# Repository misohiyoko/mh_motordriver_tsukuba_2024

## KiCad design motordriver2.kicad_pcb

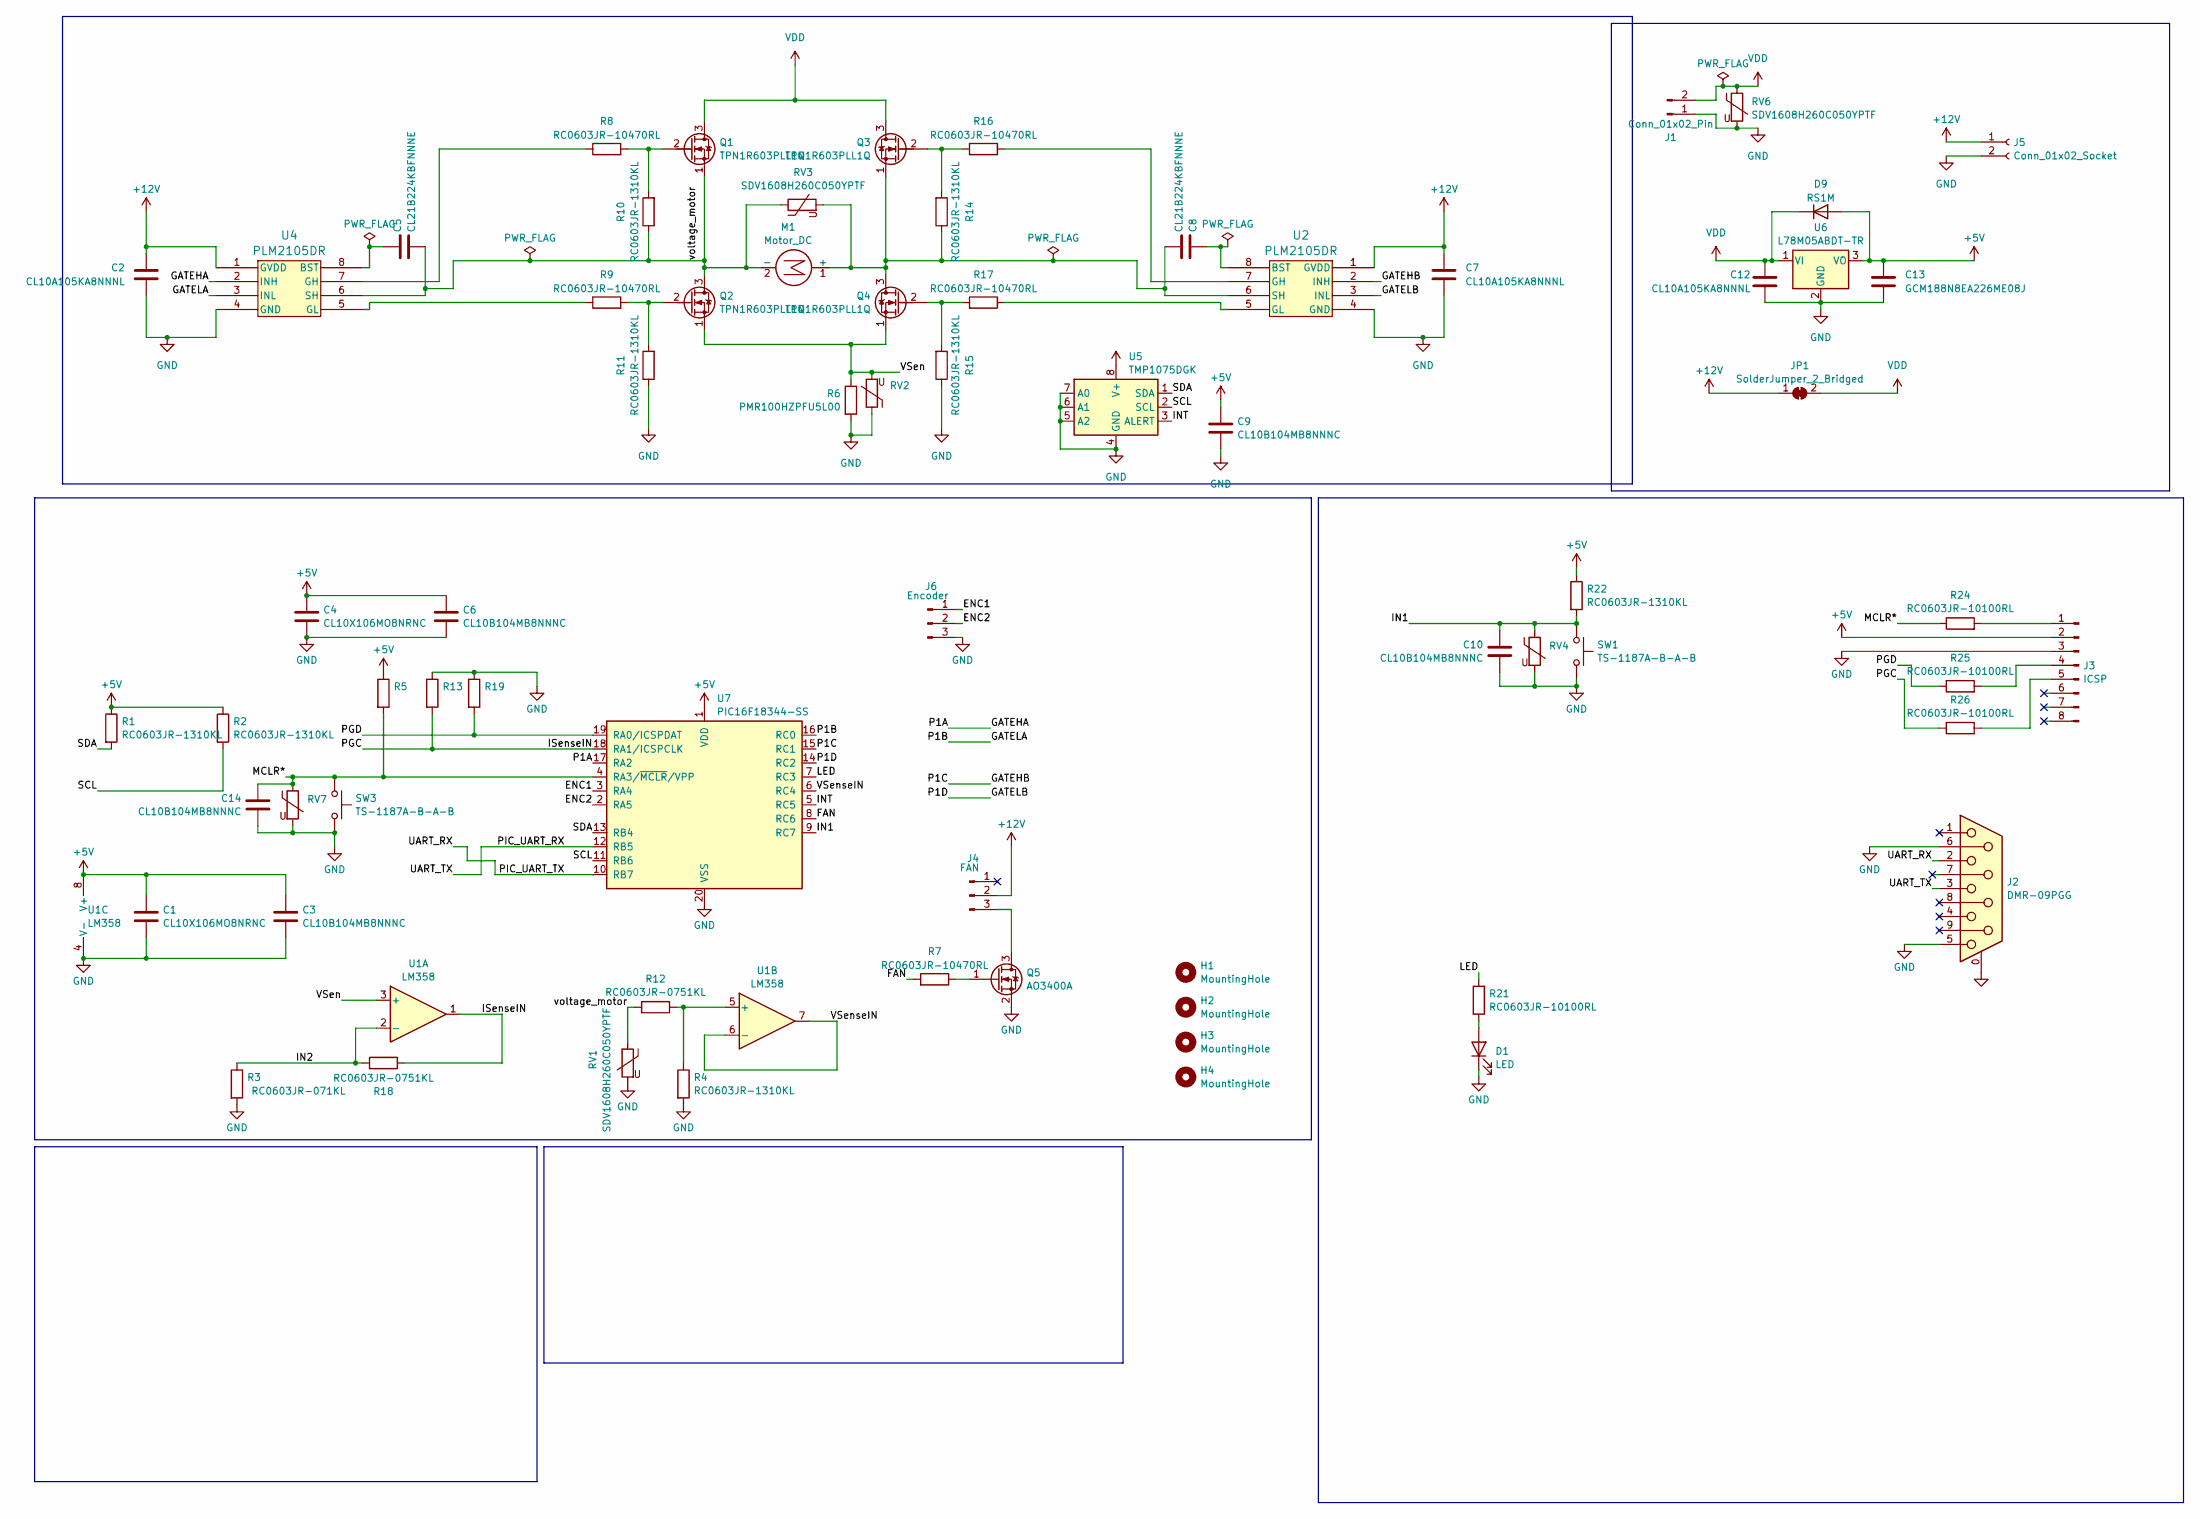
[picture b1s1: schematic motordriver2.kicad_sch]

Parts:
C1, C4: CL10X106MO8NRNC; C_0603_1608Metric; LCSC C19702
C2, C7: CL10A105KA8NNNL; C_0603_1608Metric; LCSC C15849
C3, C6, C9, C10, C14: CL10B104MB8NNNC; C_0603_1608Metric; LCSC C14663
C5, C8: CL21B224KBFNNNE; C_0805_2012Metric; LCSC C5378
C12: CL10A105KA8NNNL; C_0603_1608Metric_Pad1.08x0.95mm_HandSolder; LCSC C1848
C13: GCM188N8EA226ME08J; C_0603_1608Metric_Pad1.08x0.95mm_HandSolder; LCSC C45783
D1: LED; LED_0603_1608Metric_Pad1.05x0.95mm_HandSolder
D9: RS1M; D_SMA_Handsoldering; LCSC C8678
H1, H2, H3, H4: MountingHole; MountingHole_3.2mm_M3_Pad
J1: Conn_01x02_Pin; AMASS_XT60IPW-M_1x03_P7.20mm_Horizontal
J2: DMR-09PGG; DSUB-9_Female_Horizontal_P2.77x2.84mm_EdgePinOffset7.70mm_H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; LCSC C2846087
J3: ICSP; PinSocket_1x08_P2.54mm_Vertical
J4: FAN; PinSocket_1x03_P2.54mm_Vertical
J5: Conn_01x02_Socket; PinSocket_1x02_P2.54mm_Vertical
J6: Encoder; PinSocket_1x03_P2.54mm_Vertical
JP1: SolderJumper_2_Bridged; SolderJumper-2_P1.3mm_Bridged_RoundedPad1.0x1.5mm
M1: Motor_DC; AMASS_XT60PW-F_1x02_P7.20mm_Horizontal
Q1, Q2, Q3, Q4: TPN1R603PLL1Q; TSON Advance_TOS; LCSC C516183
Q5: AO3400A; SOT-23
R1, R2, R4, R5, R13, R19, R22: RC0603JR-1310KL; R_0603_1608Metric; LCSC C25744
R3: RC0603JR-071KL; R_0603_1608Metric
R6: PMR100HZPFU5L00; R_2512_6332Metric
R7, R8, R9, R16, R17: RC0603JR-10470RL; R_0603_1608Metric; LCSC C23182
R10, R11, R14, R15: RC0603JR-1310KL; R_0603_1608Metric; LCSC C25804
R12, R18: RC0603JR-0751KL; R_0603_1608Metric; LCSC C23196
R21, R24, R25, R26: RC0603JR-10100RL; R_0603_1608Metric; LCSC C17415
RV1, RV2, RV3, RV6: SDV1608H260C050YPTF; R_0603_1608Metric; LCSC C96738
RV4, RV7: AVR-M1005C080MTADB; R_0402_1005Metric; LCSC C92017
SW1, SW3: TS-1187A-B-A-B; SW_Push_1P1T_XKB_TS-1187A; LCSC C318884
U1: LM358; SOIC-8_3.9x4.9mm_P1.27mm; LCSC C7950
U2, U4: PLM2105DR; SOIC8_D_TEX
U5: TMP1075DGK; VSSOP-8_3.0x3.0mm_P0.65mm; LCSC C2864807
U6: L78M05ABDT-TR; TO-252-2; LCSC C58069
U7: PIC16F18344-SS; SSOP-20_5.3x7.2mm_P0.65mm

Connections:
+5V: C1.1, C3.1, C4.1, C6.1, C9.1, C13.1, D9.2 (A), J3.2, R1.1, R2.1, R5.1, R22.1, U1.8 (V+), U5.8 (V+), U6.3 (VO), U7.1 (VDD)
+12V: C2.1, C7.1, J4.2, J5.1, JP1.1 (A), U2.1 (GVDD), U4.1 (GVDD)
/ENC1: J6.1, U7.3 (RA4)
/ENC2: J6.2, U7.2 (RA5)
/FAN: R7.2, U7.8 (RC6)
/GATEHA: U4.2 (INH), U7.17 (RA2)
/GATEHB: U2.2 (INH), U7.15 (RC1)
/GATELA: U4.3 (INL), U7.16 (RC0)
/GATELB: U2.3 (INL), U7.14 (RC2)
/IN1: C10.1, R22.2, RV4.1, SW1.1, U7.9 (RC7)
/IN2: R3.1, R18.2, U1.2 (-)
/INT: U5.3 (ALERT), U7.5 (RC5)
/ISenseIN: R13.2, R18.1, R26.1, U1.1, U7.18 (RA1/ICSPCLK)
/LED: R21.2, U7.7 (RC3)
/MCLR*: C14.1, R5.2, R24.1, RV7.1, SW3.1, U7.4 (RA3/~MCLR/VPP)
/PGD: R19.2, R25.1, U7.19 (RA0/ICSPDAT)
/PIC_UART_RX: J2.3, U7.12 (RB5)
/PIC_UART_TX: J2.2, U7.10 (RB7)
/SCL: R2.2, U5.2 (SCL), U7.11 (RB6)
/SDA: R1.2, U5.1 (SDA), U7.13 (RB4)
/VSen: Q2.1 (S), Q4.1 (S), R6.1, RV2.2, U1.3 (+)
/VSenseIN: U1.6 (-), U1.7, U7.6 (RC4)
/voltage_motor: C5.1, M1.2 (-), Q1.1 (S), Q2.3 (D), R10.1, R12.1, RV1.1, RV3.1, U4.6 (SH)
GND: C1.2, C2.2, C3.2, C4.2, C6.2, C7.2, C9.2, C10.2, C12.2, C13.2, C14.2, D1.1 (K), J1.1, J2.0 (PAD), J2.5, J2.6, J3.3, J5.2, J6.3, Q5.2 (S), R3.2, R4.2, R6.2, R11.1, R13.1, R15.1, R19.1, RV1.2, RV2.1, RV4.2, RV6.2, RV7.2, SW1.2, SW3.2, U1.4 (V-), U2.4 (GND), U4.4 (GND), U5.4 (GND), U5.5 (A2), U5.6 (A1), U5.7 (A0), U6.2 (GND), U7.20 (VSS)
unnamed: D1.2 (A), R21.1
unnamed: J3.1, R24.2
unnamed: J3.4, R25.2
unnamed: J3.5, R26.2
unnamed: J4.3, Q5.3 (D)
unnamed: C8.1, M1.1 (+), Q3.1 (S), Q4.3 (D), R14.1, RV3.2, U2.6 (SH)
unnamed: Q1.2 (G), R8.2, R10.2
unnamed: Q2.2 (G), R9.2, R11.2
unnamed: Q3.2 (G), R14.2, R16.2
unnamed: Q4.2 (G), R15.2, R17.2
unnamed: Q5.1 (G), R7.1
unnamed: R4.1, R12.2, U1.5 (+)
unnamed: C8.2, U2.8 (BST)
unnamed: R16.1, U2.7 (GH)
unnamed: R17.1, U2.5 (GL)
unnamed: C5.2, U4.8 (BST)
unnamed: R8.1, U4.7 (GH)
unnamed: R9.1, U4.5 (GL)
VDD: C12.1, D9.1 (K), J1.2, JP1.2 (B), Q1.3 (D), Q3.3 (D), RV6.1, U6.1 (VI)

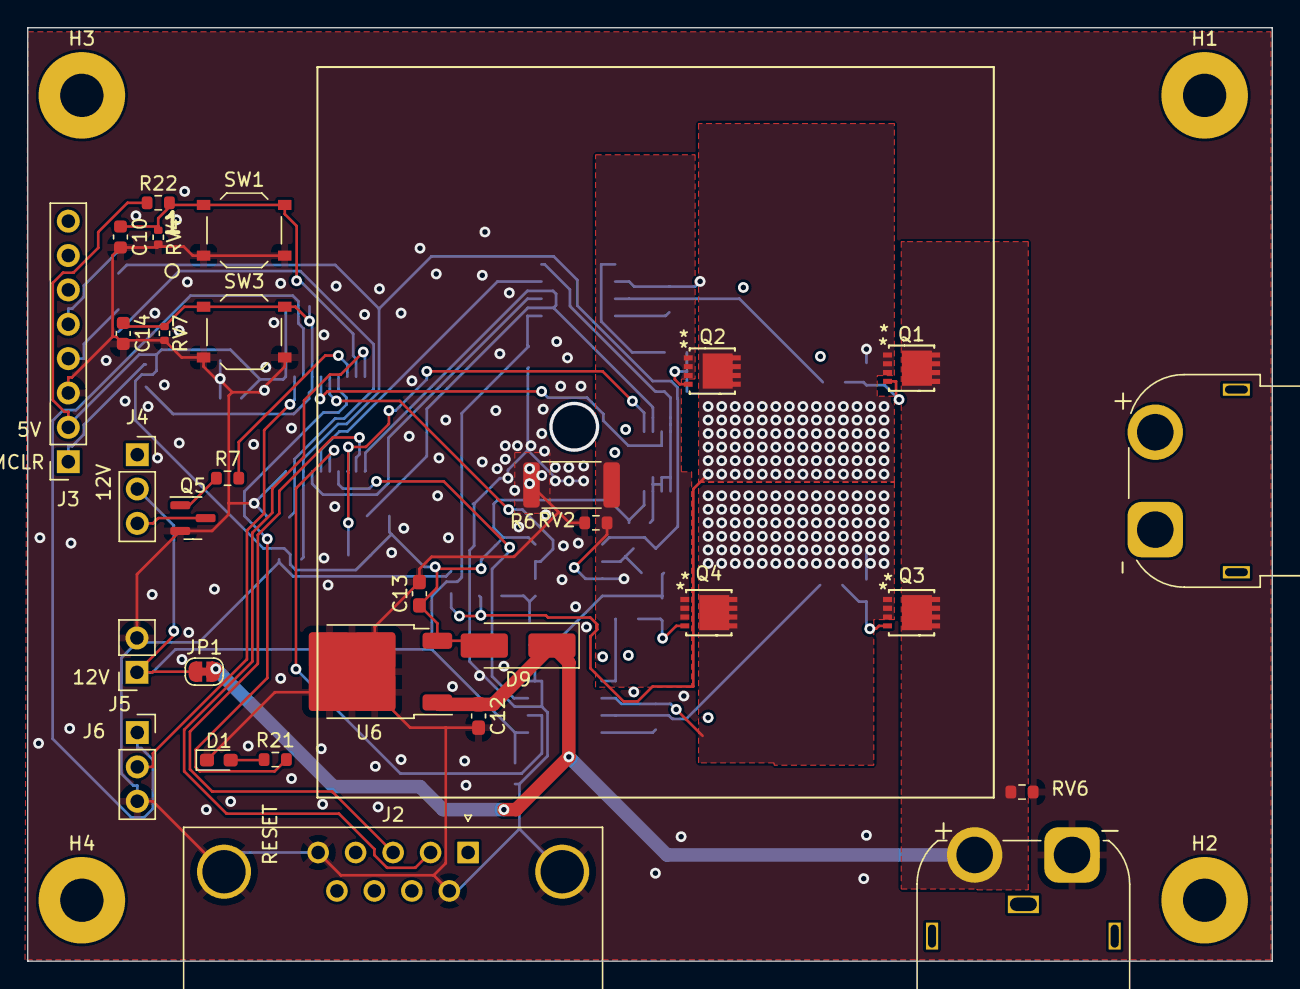
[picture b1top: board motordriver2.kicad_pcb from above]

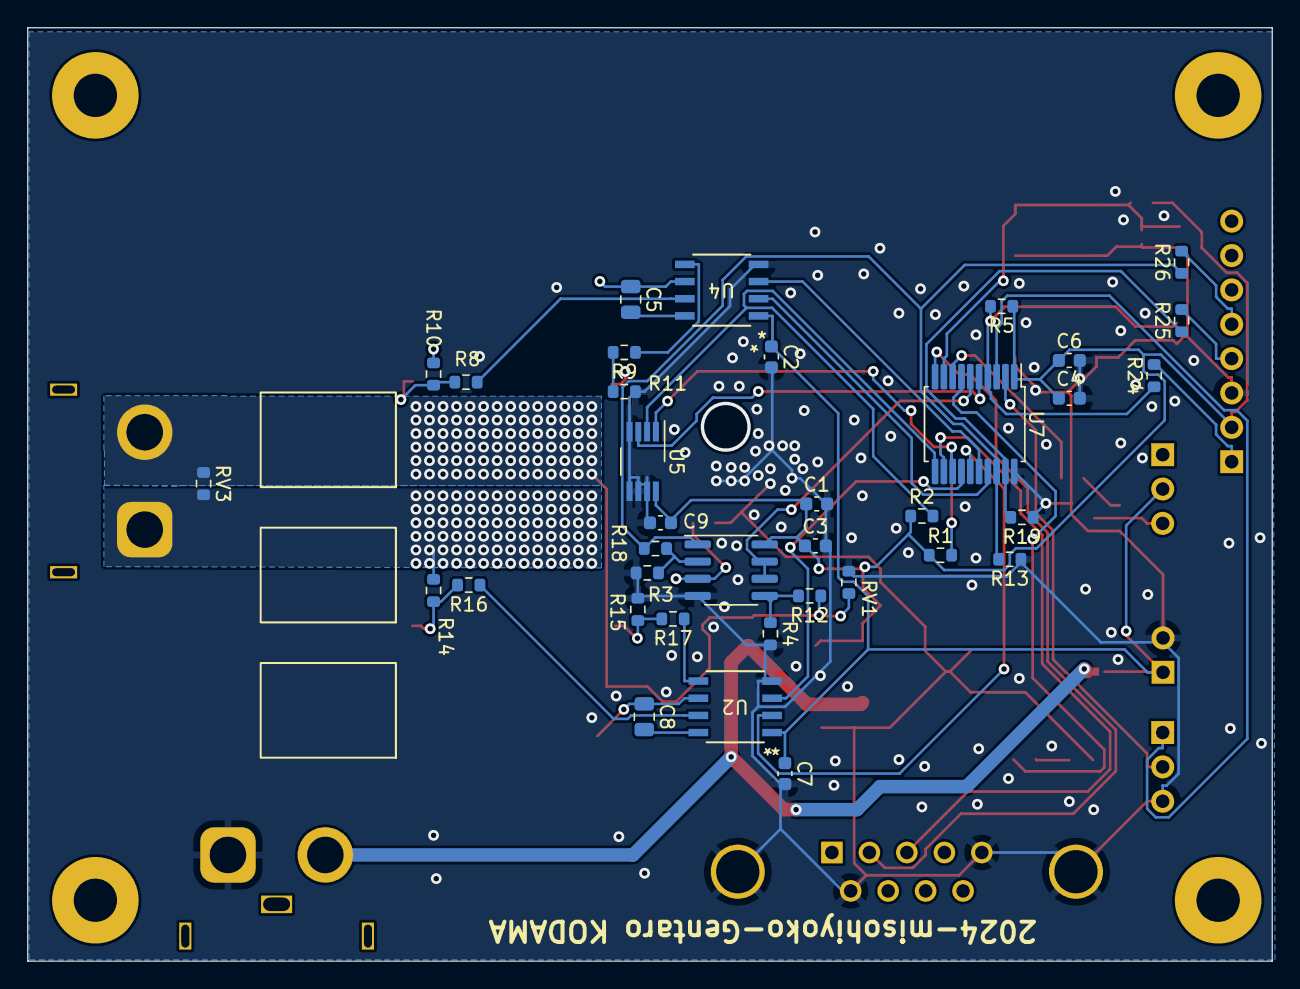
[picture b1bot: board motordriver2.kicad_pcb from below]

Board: 2 copper layers, 92.0 x 69.0 mm, 70 parts (36 on the bottom side), 43 nets.

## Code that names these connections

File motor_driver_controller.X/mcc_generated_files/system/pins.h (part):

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// get/set IO_RA1 aliases
#define IO_RA1_TRIS                 TRISAbits.TRISA1
#define IO_RA1_LAT                  LATAbits.LATA1
#define IO_RA1_PORT                 PORTAbits.RA1
#define IO_RA1_WPU                  WPUAbits.WPUA1
#define IO_RA1_OD                   ODCONAbits.ODCA1
#define IO_RA1_ANS                  ANSELAbits.ANSA1
#define IO_RA1_SetHigh()            do { LATAbits.LATA1 = 1; } while(0)
#define IO_RA1_SetLow()             do { LATAbits.LATA1 = 0; } while(0)
#define IO_RA1_Toggle()             do { LATAbits.LATA1 = ~LATAbits.LATA1; } while(0)
#define IO_RA1_GetValue()           PORTAbits.RA1
#define IO_RA1_SetDigitalInput()    do { TRISAbits.TRISA1 = 1; } while(0)
#define IO_RA1_SetDigitalOutput()   do { TRISAbits.TRISA1 = 0; } while(0)
#define IO_RA1_SetPullup()          do { WPUAbits.WPUA1 = 1; } while(0)
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// get/set IO_RA2 aliases
#define IO_RA2_TRIS                 TRISAbits.TRISA2
#define IO_RA2_LAT                  LATAbits.LATA2
#define IO_RA2_PORT                 PORTAbits.RA2
#define IO_RA2_WPU                  WPUAbits.WPUA2
#define IO_RA2_OD                   ODCONAbits.ODCA2
#define IO_RA2_ANS                  ANSELAbits.ANSA2
#define IO_RA2_SetHigh()            do { LATAbits.LATA2 = 1; } while(0)
#define IO_RA2_SetLow()             do { LATAbits.LATA2 = 0; } while(0)
#define IO_RA2_Toggle()             do { LATAbits.LATA2 = ~LATAbits.LATA2; } while(0)
#define IO_RA2_GetValue()           PORTAbits.RA2
#define IO_RA2_SetDigitalInput()    do { TRISAbits.TRISA2 = 1; } while(0)
#define IO_RA2_SetDigitalOutput()   do { TRISAbits.TRISA2 = 0; } while(0)
#define IO_RA2_SetPullup()          do { WPUAbits.WPUA2 = 1; } while(0)
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// get/set IO_RA4 aliases
#define IO_RA4_TRIS                 TRISAbits.TRISA4
#define IO_RA4_LAT                  LATAbits.LATA4
#define IO_RA4_PORT                 PORTAbits.RA4
#define IO_RA4_WPU                  WPUAbits.WPUA4
#define IO_RA4_OD                   ODCONAbits.ODCA4
#define IO_RA4_ANS                  ANSELAbits.ANSA4
#define IO_RA4_SetHigh()            do { LATAbits.LATA4 = 1; } while(0)
#define IO_RA4_SetLow()             do { LATAbits.LATA4 = 0; } while(0)
#define IO_RA4_Toggle()             do { LATAbits.LATA4 = ~LATAbits.LATA4; } while(0)
#define IO_RA4_GetValue()           PORTAbits.RA4
#define IO_RA4_SetDigitalInput()    do { TRISAbits.TRISA4 = 1; } while(0)
#define IO_RA4_SetDigitalOutput()   do { TRISAbits.TRISA4 = 0; } while(0)
#define IO_RA4_SetPullup()          do { WPUAbits.WPUA4 = 1; } while(0)
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// get/set IO_RA5 aliases
#define IO_RA5_TRIS                 TRISAbits.TRISA5
#define IO_RA5_LAT                  LATAbits.LATA5
#define IO_RA5_PORT                 PORTAbits.RA5
#define IO_RA5_WPU                  WPUAbits.WPUA5
#define IO_RA5_OD                   ODCONAbits.ODCA5
#define IO_RA5_ANS                  ANSELAbits.ANSA5
#define IO_RA5_SetHigh()            do { LATAbits.LATA5 = 1; } while(0)
#define IO_RA5_SetLow()             do { LATAbits.LATA5 = 0; } while(0)
#define IO_RA5_Toggle()             do { LATAbits.LATA5 = ~LATAbits.LATA5; } while(0)
#define IO_RA5_GetValue()           PORTAbits.RA5
#define IO_RA5_SetDigitalInput()    do { TRISAbits.TRISA5 = 1; } while(0)
#define IO_RA5_SetDigitalOutput()   do { TRISAbits.TRISA5 = 0; } while(0)
#define IO_RA5_SetPullup()          do { WPUAbits.WPUA5 = 1; } while(0)
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// get/set IO_RB4 aliases
#define IO_RB4_TRIS                 TRISBbits.TRISB4
#define IO_RB4_LAT                  LATBbits.LATB4
#define IO_RB4_PORT                 PORTBbits.RB4
#define IO_RB4_WPU                  WPUBbits.WPUB4
#define IO_RB4_OD                   ODCONBbits.ODCB4
#define IO_RB4_ANS                  ANSELBbits.ANSB4
#define IO_RB4_SetHigh()            do { LATBbits.LATB4 = 1; } while(0)
#define IO_RB4_SetLow()             do { LATBbits.LATB4 = 0; } while(0)
#define IO_RB4_Toggle()             do { LATBbits.LATB4 = ~LATBbits.LATB4; } while(0)
#define IO_RB4_GetValue()           PORTBbits.RB4
#define IO_RB4_SetDigitalInput()    do { TRISBbits.TRISB4 = 1; } while(0)
#define IO_RB4_SetDigitalOutput()   do { TRISBbits.TRISB4 = 0; } while(0)
#define IO_RB4_SetPullup()          do { WPUBbits.WPUB4 = 1; } while(0)
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// get/set IO_RB5 aliases
#define IO_RB5_TRIS                 TRISBbits.TRISB5
#define IO_RB5_LAT                  LATBbits.LATB5
#define IO_RB5_PORT                 PORTBbits.RB5
#define IO_RB5_WPU                  WPUBbits.WPUB5
#define IO_RB5_OD                   ODCONBbits.ODCB5
#define IO_RB5_ANS                  ANSELBbits.ANSB5
#define IO_RB5_SetHigh()            do { LATBbits.LATB5 = 1; } while(0)
#define IO_RB5_SetLow()             do { LATBbits.LATB5 = 0; } while(0)
#define IO_RB5_Toggle()             do { LATBbits.LATB5 = ~LATBbits.LATB5; } while(0)
#define IO_RB5_GetValue()           PORTBbits.RB5
#define IO_RB5_SetDigitalInput()    do { TRISBbits.TRISB5 = 1; } while(0)
#define IO_RB5_SetDigitalOutput()   do { TRISBbits.TRISB5 = 0; } while(0)
#define IO_RB5_SetPullup()          do { WPUBbits.WPUB5 = 1; } while(0)
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// get/set IO_RB6 aliases
#define IO_RB6_TRIS                 TRISBbits.TRISB6
#define IO_RB6_LAT                  LATBbits.LATB6
#define IO_RB6_PORT                 PORTBbits.RB6
#define IO_RB6_WPU                  WPUBbits.WPUB6
#define IO_RB6_OD                   ODCONBbits.ODCB6
#define IO_RB6_ANS                  ANSELBbits.ANSB6
#define IO_RB6_SetHigh()            do { LATBbits.LATB6 = 1; } while(0)
#define IO_RB6_SetLow()             do { LATBbits.LATB6 = 0; } while(0)
#define IO_RB6_Toggle()             do { LATBbits.LATB6 = ~LATBbits.LATB6; } while(0)
#define IO_RB6_GetValue()           PORTBbits.RB6
#define IO_RB6_SetDigitalInput()    do { TRISBbits.TRISB6 = 1; } while(0)
#define IO_RB6_SetDigitalOutput()   do { TRISBbits.TRISB6 = 0; } while(0)
#define IO_RB6_SetPullup()          do { WPUBbits.WPUB6 = 1; } while(0)
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// get/set IO_RB7 aliases
#define IO_RB7_TRIS                 TRISBbits.TRISB7
#define IO_RB7_LAT                  LATBbits.LATB7
#define IO_RB7_PORT                 PORTBbits.RB7
#define IO_RB7_WPU                  WPUBbits.WPUB7
#define IO_RB7_OD                   ODCONBbits.ODCB7
#define IO_RB7_ANS                  ANSELBbits.ANSB7
#define IO_RB7_SetHigh()            do { LATBbits.LATB7 = 1; } while(0)
#define IO_RB7_SetLow()             do { LATBbits.LATB7 = 0; } while(0)
#define IO_RB7_Toggle()             do { LATBbits.LATB7 = ~LATBbits.LATB7; } while(0)
#define IO_RB7_GetValue()           PORTBbits.RB7
#define IO_RB7_SetDigitalInput()    do { TRISBbits.TRISB7 = 1; } while(0)
#define IO_RB7_SetDigitalOutput()   do { TRISBbits.TRISB7 = 0; } while(0)
#define IO_RB7_SetPullup()          do { WPUBbits.WPUB7 = 1; } while(0)
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// get/set IO_RC0 aliases
#define IO_RC0_TRIS                 TRISCbits.TRISC0
#define IO_RC0_LAT                  LATCbits.LATC0
#define IO_RC0_PORT                 PORTCbits.RC0
#define IO_RC0_WPU                  WPUCbits.WPUC0
#define IO_RC0_OD                   ODCONCbits.ODCC0
#define IO_RC0_ANS                  ANSELCbits.ANSC0
#define IO_RC0_SetHigh()            do { LATCbits.LATC0 = 1; } while(0)
#define IO_RC0_SetLow()             do { LATCbits.LATC0 = 0; } while(0)
#define IO_RC0_Toggle()             do { LATCbits.LATC0 = ~LATCbits.LATC0; } while(0)
#define IO_RC0_GetValue()           PORTCbits.RC0
#define IO_RC0_SetDigitalInput()    do { TRISCbits.TRISC0 = 1; } while(0)
#define IO_RC0_SetDigitalOutput()   do { TRISCbits.TRISC0 = 0; } while(0)
#define IO_RC0_SetPullup()          do { WPUCbits.WPUC0 = 1; } while(0)
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// get/set IO_RC1 aliases
#define IO_RC1_TRIS                 TRISCbits.TRISC1
#define IO_RC1_LAT                  LATCbits.LATC1
#define IO_RC1_PORT                 PORTCbits.RC1
#define IO_RC1_WPU                  WPUCbits.WPUC1
#define IO_RC1_OD                   ODCONCbits.ODCC1
#define IO_RC1_ANS                  ANSELCbits.ANSC1
#define IO_RC1_SetHigh()            do { LATCbits.LATC1 = 1; } while(0)
#define IO_RC1_SetLow()             do { LATCbits.LATC1 = 0; } while(0)
#define IO_RC1_Toggle()             do { LATCbits.LATC1 = ~LATCbits.LATC1; } while(0)
#define IO_RC1_GetValue()           PORTCbits.RC1
#define IO_RC1_SetDigitalInput()    do { TRISCbits.TRISC1 = 1; } while(0)
#define IO_RC1_SetDigitalOutput()   do { TRISCbits.TRISC1 = 0; } while(0)
#define IO_RC1_SetPullup()          do { WPUCbits.WPUC1 = 1; } while(0)
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// get/set IO_RC2 aliases
#define IO_RC2_TRIS                 TRISCbits.TRISC2
#define IO_RC2_LAT                  LATCbits.LATC2
#define IO_RC2_PORT                 PORTCbits.RC2
#define IO_RC2_WPU                  WPUCbits.WPUC2
#define IO_RC2_OD                   ODCONCbits.ODCC2
#define IO_RC2_ANS                  ANSELCbits.ANSC2
#define IO_RC2_SetHigh()            do { LATCbits.LATC2 = 1; } while(0)
#define IO_RC2_SetLow()             do { LATCbits.LATC2 = 0; } while(0)
#define IO_RC2_Toggle()             do { LATCbits.LATC2 = ~LATCbits.LATC2; } while(0)
#define IO_RC2_GetValue()           PORTCbits.RC2
#define IO_RC2_SetDigitalInput()    do { TRISCbits.TRISC2 = 1; } while(0)
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
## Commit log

2024-03-20 add power source
2024-03-20 add xt60
2024-03-23 comp10*10
2024-03-23 small
2024-04-24 change
2024-07-11 add production
2024-07-12 new mc
2024-07-12 add mssp

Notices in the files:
motor_driver_controller.X/mcc_generated_files/system/pins.h:
© [2024] Microchip Technology Inc. and its subsidiaries.
